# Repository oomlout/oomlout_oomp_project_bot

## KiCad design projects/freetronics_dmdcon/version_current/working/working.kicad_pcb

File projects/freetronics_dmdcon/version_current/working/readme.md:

# DMDCon by freetronics  
This is a harvested standardized copy of a project from github.  
The original project can be found at:  
https://github.com/freetronics/DMDCon  
Please consult that link for additional, details, files, and license information.  
Note: It was auto harvested and if the original repo had more than one board file or anything out of the ordinary the files here are likely not representative.

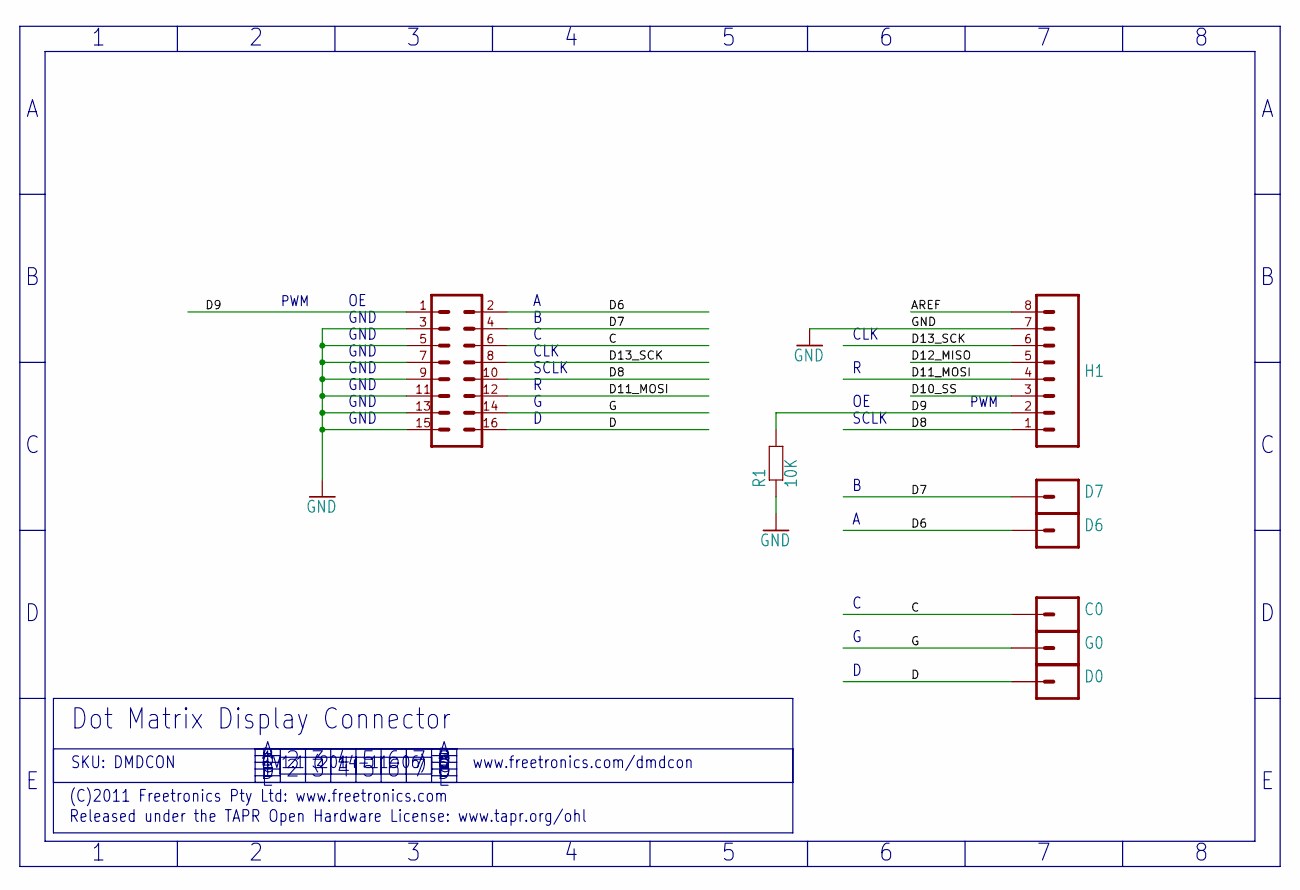
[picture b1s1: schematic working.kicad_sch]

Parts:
C0: M01PTH; 1X01
D0, D6, D7: M01PTH; 1X01
DMD0: M08X2SMALLERPADS; 2X8-SMALLERPADS
G0: M01PTH; 1X01
H1: Digital_8_13; 1X08
R1: 10K; 0805

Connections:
AREF: H1.8
C: C0.1, DMD0.6
D: D0.1, DMD0.16
D6: D6.1, DMD0.2
D7: D7.1, DMD0.4
D8: DMD0.10, H1.1
D9: DMD0.1, H1.2, R1.2
D10_SS: H1.3
D11_MOSI: DMD0.12, H1.4
D12_MISO: H1.5
D13_SCK: DMD0.8, H1.6
G: DMD0.14, G0.1
GND: DMD0.3, DMD0.5, DMD0.7, DMD0.9, DMD0.11, DMD0.13, DMD0.15, H1.7, R1.1

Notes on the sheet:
PWM
(C)2011 Freetronics Pty Ltd: www.freetronics.com
GND
CLK
www.freetronics.com/dmdcon
V1.1 (2014-11-06)
Released under the TAPR Open Hardware License: www.tapr.org/ohl
SCLK
SKU: DMDCON
Dot Matrix Display Connector

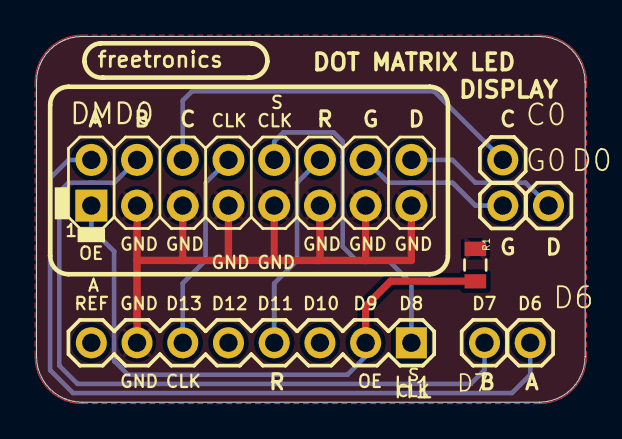
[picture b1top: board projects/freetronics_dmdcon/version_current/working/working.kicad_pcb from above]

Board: 2 copper layers, 30.5 x 20.3 mm, 8 parts (0 on the bottom side), 10 nets.

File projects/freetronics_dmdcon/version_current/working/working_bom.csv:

"Id";"Designator";"Footprint";"Quantity";"Designation";"Supplier and ref";
1;"DMD0";"2X8-SMALLERPADS";1;"M08X2";;;
2;"D7,G0,D0,C0,D6";"1X01";5;"M01PTH";;;
3;"R1";"0805";1;"10K";;;
4;"H1";"1X08";1;"Digital_8_13";;;

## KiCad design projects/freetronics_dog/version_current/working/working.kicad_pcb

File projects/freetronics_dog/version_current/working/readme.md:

# DOG by freetronics  
This is a harvested standardized copy of a project from github.  
The original project can be found at:  
https://github.com/freetronics/DOG  
Please consult that link for additional, details, files, and license information.  
Note: It was auto harvested and if the original repo had more than one board file or anything out of the ordinary the files here are likely not representative.

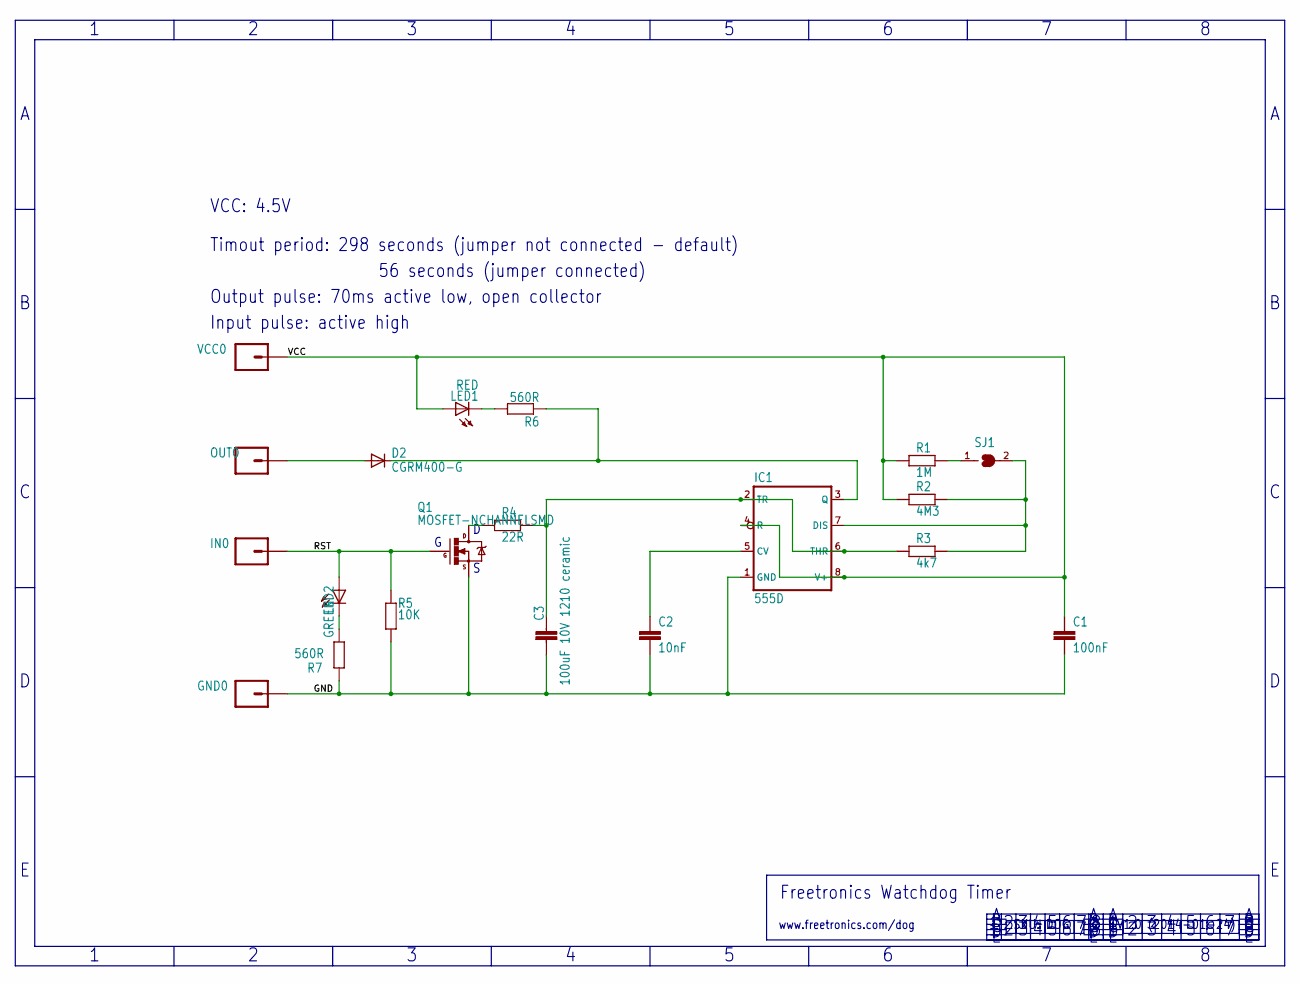
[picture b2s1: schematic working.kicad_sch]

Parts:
C1: 100nF; 0603
C2: 10nF; 0603
C3: 100uF 10V 1210 ceramic; C1210
D2: CGRM400-G; SOD-123_MINI-SMA
GND0: M01PTH; 1X01
IC1: 555D; SO08
IN0: M01PTH; 1X01
LED1: RED; LED-0603
LED2: GREEN; LED-0603
OUT0: M01PTH; 1X01
Q1: MOSFET-NCHANNELSMD; SOT23-3
R1: 1M; 0603
R2: 4M3; 0603
R3: 4k7; 0603
R4: 22R; 0603
R5: 10K; 0603
R6, R7: 560R; 0603
SJ1: SJ
VCC0: M01PTH; 1X01

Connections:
C4: C3.1, IC1.2 (TR), IC1.6 (THR), R3.1, R4.2
GND: C1.2, C2.2, C3.2, GND0.1, IC1.1 (GND), Q1.2 (S), R5.1, R7.2
unnamed: Q1.3 (D), R4.1
unnamed: LED2.C, R7.1
unnamed: R1.2, SJ1.1
unnamed: IC1.7 (DIS), R2.2, R3.2, SJ1.2
unnamed: LED1.C, R6.2
unnamed: C2.1, IC1.5 (CV)
unnamed: D2.A, OUT0.1
RST: IN0.1, LED2.A, Q1.1 (G), R5.2
TO: D2.C, IC1.3 (Q), R6.1
VCC: C1.1, IC1.4 (R), IC1.8 (V+), LED1.A, R1.1, R2.1, VCC0.1

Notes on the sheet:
V1.0 (2014-01-24)
VCC: 4.5V
www.freetronics.com/dog
Input pulse: active high
Timout period: 298 seconds (jumper not connected - default)
SKU: DOG
56 seconds (jumper connected)
Freetronics Watchdog Timer
Output pulse: 70ms active low, open collector

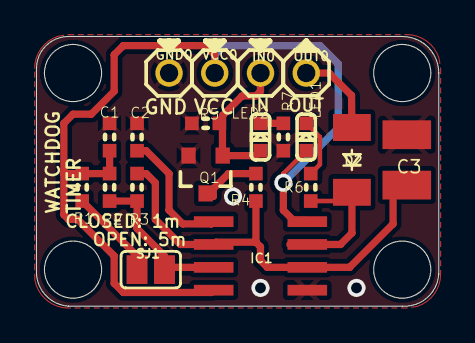
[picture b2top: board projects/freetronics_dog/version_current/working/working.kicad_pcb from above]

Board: 2 copper layers, 22.4 x 15.0 mm, 24 parts (0 on the bottom side), 12 nets.

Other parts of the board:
@HOLE0, @HOLE1, @HOLE2, @HOLE3: (no value)

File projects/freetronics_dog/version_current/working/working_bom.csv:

"Id";"Designator";"Footprint";"Quantity";"Designation";"Supplier and ref";
1;"R2";"0603";1;"4M3";;;
2;"R3";"0603";1;"4k7";;;
3;"VCC0,IN0,GND0,OUT0";"1X01";4;"M01PTH";;;
4;"@HOLE1,@HOLE0,@HOLE2,@HOLE3";"";4;"";;;
5;"C2";"0603";1;"10nF";;;
6;"IC1";"SO08";1;"LM555D";;;
7;"Q1";"SOT23-3";1;"2N7002";;;
8;"LED1";"LED-0603";1;"RED";;;
9;"R6,R7";"0603";2;"560R";;;
10;"R5";"0603";1;"10K";;;
11;"R1";"0603";1;"1M";;;
12;"SJ1";"SJ";1;"";;;
13;"C3";"C1210";1;"100uF 10V 1210 ceramic";;;
14;"LED2";"LED-0603";1;"GREEN";;;
15;"D2";"SOD-123_MINI-SMA";1;"CGRM4001-G";;;
16;"C1";"0603";1;"100nF";;;
17;"R4";"0603";1;"22R";;;

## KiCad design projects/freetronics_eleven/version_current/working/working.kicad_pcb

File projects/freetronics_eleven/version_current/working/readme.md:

# Eleven by freetronics  
This is a harvested standardized copy of a project from github.  
The original project can be found at:  
https://github.com/freetronics/Eleven  
Please consult that link for additional, details, files, and license information.  
Note: It was auto harvested and if the original repo had more than one board file or anything out of the ordinary the files here are likely not representative.

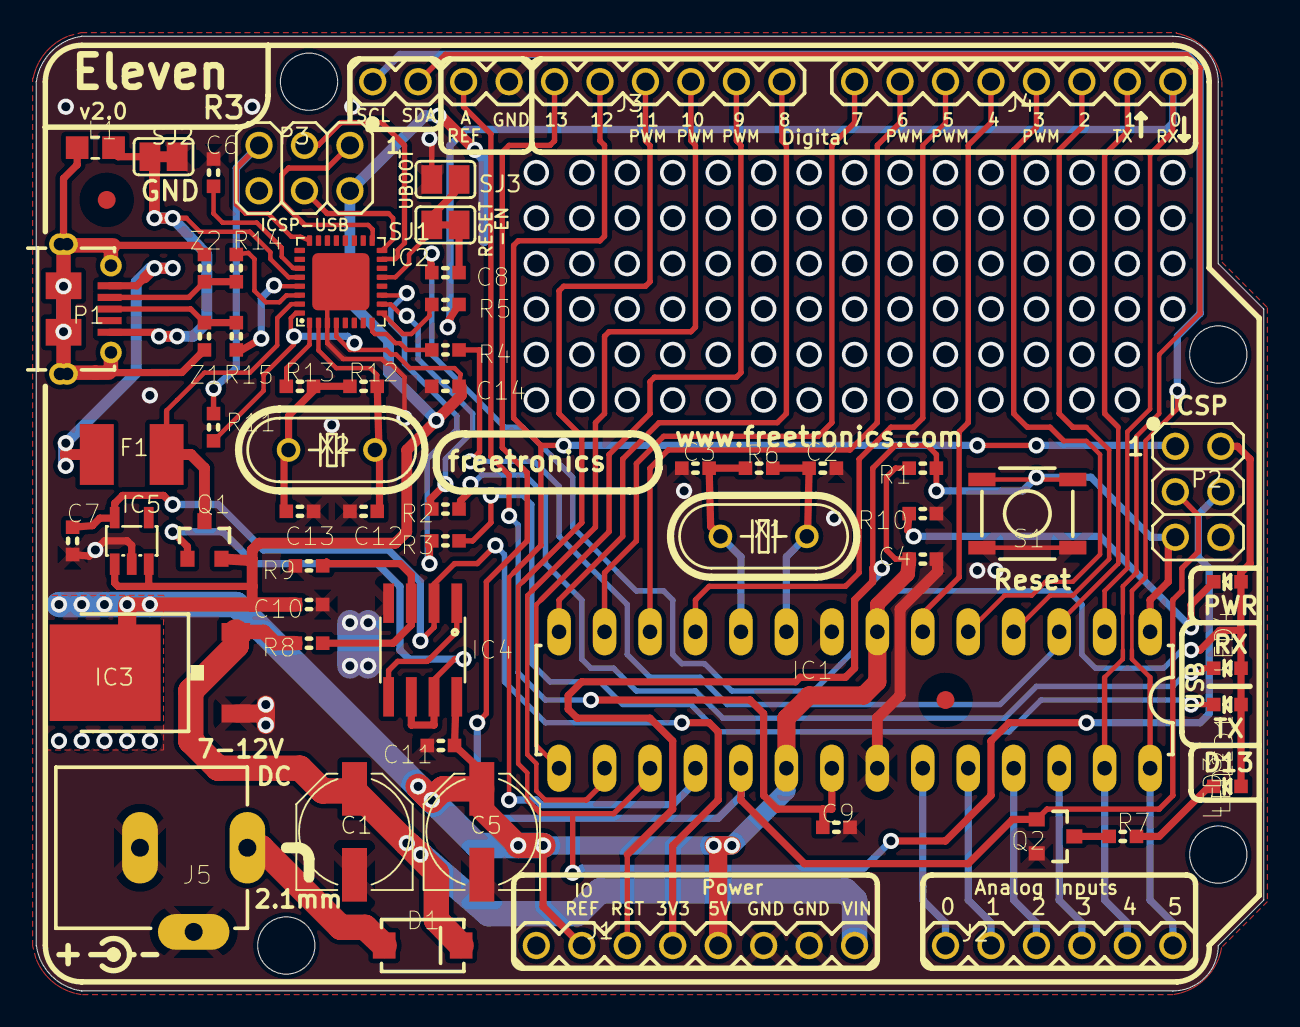
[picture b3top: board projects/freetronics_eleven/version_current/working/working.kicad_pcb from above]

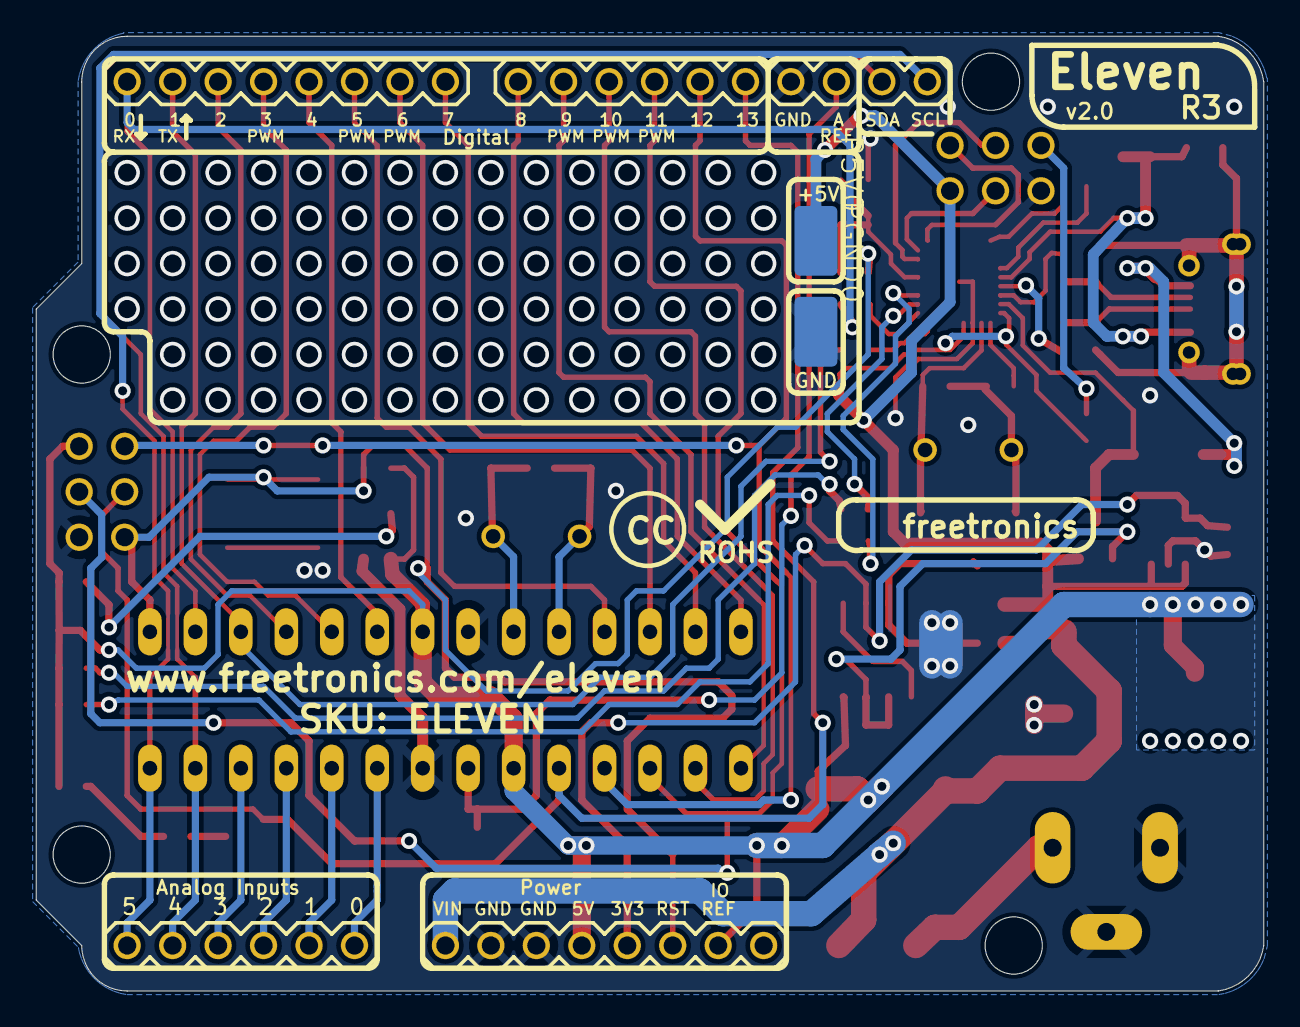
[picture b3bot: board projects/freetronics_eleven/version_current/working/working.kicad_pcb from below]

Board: 16 copper layers, 68.6 x 53.3 mm, 67 parts (2 on the bottom side), 59 nets.

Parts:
@HOLE0, @HOLE1, @HOLE2, @HOLE3: (no value)
C1, C5: 47uF 25V; PANASONIC_D
C2, C3, C12, C13: 22pF 0603; C0603
C4, C8, C9, C10, C11, C14: 100nF 0603; C0603
C6, C7: 1uF 0603; C0603
D1: 1N4004 SMB; SMA-DIODE
F1: 500mA PTC 1812; L1812
IC1: ATMEGA328P; DIL28-3
IC2: ATMEGA16U2-MU; ATMEL_QFN32
IC3: MC33269DT-5.0; DPACK
IC4: LM358D; SO08
IC5: LP2985-33DBVR; TEXAS_SOT23-DBV
J1: Power; 1X08-S
J2: Analog; 1X06-S
J3: Digital_8_13; 1X10-S
J4: Digital_0_7; 1X08-S
J5: DC_2_1MM; POWER_JACK_SLOTS
L1: 0805 INDUCTOR; 0805-LARGE
LED1: RX/GRN; LED-0603
LED2: TX/YEL; LED-0603
LED3: D13/RED; LED-0603
LED4: PWR/BLUE; LED-0603
P1: USB-6P-SMT; USB-MICROB-MB05PMXX
P2: ICSP:MAIN; 2X03PTH
P3: ICSP:USB; 2X03PTH
P5V0: LUXEON-PAD
PGND0: LUXEON-PAD
Q1: FDN340P; SOT23-3
Q2: 2N7002; SOT23-3
R1, R8, R9, R11: 10K 0603; R0603
R2, R3, R4, R5, R7, R10: 1K 0603; R0603
R6, R12: 1M 0603; R0603
R13: 27R 0603; R0603
R14, R15: 22R 0603; R0603
S1: RESET; TACTILE_SMD-6MM
SJ1: RESET-EN; SJ
SJ2: GROUND; SJ
SJ3: UBOOT; SJ
U$5, U$14: FIDUCIAL1X2.5; FIDUCIAL-1X2.5
X1, X2: 16MHz; HC49U-V
Z1, Z2: PGB1010603; TVS0603

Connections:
3V3: C7.2, IC4.2, IC5.5, J1.4
5V: C4.1, C5.+, C10.1, C11.1, C14.1, IC1.7, IC1.20, IC2.4, IC2.32, IC3.2, IC4.8, IC5.1, IC5.3, J1.2, J1.5, LED1.A, LED2.A, LED3.A, LED4.A, P2.2, P3.2, P5V0.P$1, Q1.2, R1.2, R11.2
A0: IC1.23, J2.1
A1: IC1.24, J2.2
A2: IC1.25, J2.3
A3: IC1.26, J2.4
A4_SDA: IC1.27, J2.5, J3.9
A5_SCL: IC1.28, J2.6, J3.10
AREF: C9.1, IC1.21, J3.8
D0_RX: IC1.2, J4.1, R5.1
D1_TX: IC1.3, J4.2, R4.1
D2: IC1.4, J4.3
D3: IC1.5, J4.4
D4: IC1.6, J4.5
D5: IC1.11, J4.6
D6: IC1.12, J4.7
D7: IC1.13, J4.8
D8: IC1.14, J3.1
D9: IC1.15, J3.2
D10: IC1.16, J3.3
D11_MOSI: IC1.17, J3.4, P2.4
D12_MISO: IC1.18, J3.5, P2.1
D13_SCK: IC1.19, J3.6, P2.3, Q2.1
DTR: IC2.13, SJ1.1, SJ3.2
GND: C1.-, C2.1, C3.1, C4.2, C5.-, C6.2, C7.1, C9.2, C10.2, C11.2, C12.1, C13.1, C14.2, IC1.8, IC1.22, IC2.3, IC2.EXP, IC3.1, IC4.4, IC5.2, J1.6, J1.7, J3.7, J5.GND, J5.GNDBREAK, P2.6, P3.6, PGND0.P$1, Q2.2, R9.1, R10.1, S1.1, S1.2, SJ2.2, SJ3.1
MISO2: IC2.17, P3.1
MOSI2: IC2.16, P3.4
unnamed: C8.1, SJ1.2
unnamed: IC2.1, R13.1
unnamed: L1.1, P1.FIX1, P1.FIX2, P1.PIN1, P1.PIN2, P1.TAB1, P1.TAB2, Z1.2, Z2.2
unnamed: LED3.C, R7.2
unnamed: C2.2, IC1.9, R6.2, X1.2
unnamed: Q2.3, R7.1
unnamed: C3.2, IC1.10, R6.1, X1.1
unnamed: D1.A, J5.PWR
unnamed: IC4.3, R8.1, R9.2
unnamed: IC4.1, IC4.5
unnamed: LED1.C, R2.2
unnamed: IC4.6, IC4.7, Q1.1
unnamed: LED2.C, R3.2
unnamed: LED4.C, R10.2
unnamed: P1.D+, R15.2, Z1.1
unnamed: P1.D-, R14.2, Z2.1
unnamed: C12.2, IC2.2, R12.2, X2.2
unnamed: C13.2, R12.1, R13.2, X2.1
unnamed: F1.1, P1.VBUS
unnamed: C6.1, IC2.27
RD+: IC2.29, R15.1
RD-: IC2.30, R14.1
RESET: C8.2, IC1.1, J1.3, P2.5, R1.1, S1.3, S1.4
RESET2: IC2.24, P3.5, R11.1
RXLED: IC2.10, R2.1
SCK2: IC2.15, P3.3
TXLED: IC2.11, R3.1
UGND: IC2.28, L1.2, P1.GND, SJ2.1
USBRXD: IC2.9, R5.2
USBTXD: IC2.8, R4.2
USBVCC: F1.2, IC2.31, Q1.3
VIN: C1.+, D1.C, IC3.3, J1.8, R8.2

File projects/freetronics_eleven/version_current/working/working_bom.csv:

"Id";"Designator";"Footprint";"Quantity";"Designation";"Supplier and ref";
1;"R2,R10,R4,R3,R7,R5";"R0603";6;"1K 0603";;;
2;"C8,C4,C9,C14,C10,C11";"C0603";6;"100nF 0603";;;
3;"X2,X1";"HC49U-V";2;"16MHz";;;
4;"R6,R12";"R0603";2;"1M 0603";;;
5;"R9,R8,R1,R11";"R0603";4;"10K 0603";;;
6;"J3";"1X10-S";1;"Digital_8_13";;;
7;"Q2";"SOT23-3";1;"2N7002";;;
8;"IC2";"ATMEL_QFN32";1;"ATMEGA16U2-MU";;;
9;"R13";"R0603";1;"27R 0603";;;
10;"SJ2";"SJ";1;"GROUND";;;
11;"P3";"2X03PTH";1;"ICSP:USB";;;
12;"C1,C5";"PANASONIC_D";2;"47uF 25V";;;
13;"LED1";"LED-0603";1;"RX/GRN";;;
14;"J4";"1X08-S";1;"Digital_0_7";;;
15;"L1";"0805-LARGE";1;"0805 INDUCTOR";;;
16;"LED4";"LED-0603";1;"PWR/BLUE";;;
17;"Z1,Z2";"TVS0603";2;"PGB1010603";;;
18;"C6,C7";"C0603";2;"1uF 0603";;;
19;"P1";"USB-MICROB-MB05PMXX";1;"USB-6P-SMT";;;
20;"@HOLE0,@HOLE1,@HOLE3,@HOLE2";"";4;"";;;
21;"SJ1";"SJ";1;"RESET-EN";;;
22;"F1";"L1812";1;"500mA PTC 1812";;;
23;"C3,C12,C13,C2";"C0603";4;"22pF 0603";;;
24;"J1";"1X08-S";1;"Power";;;
25;"LED2";"LED-0603";1;"TX/YEL";;;
26;"LED3";"LED-0603";1;"D13/RED";;;
27;"IC3";"DPACK";1;"MC33269DT-5.0";;;
28;"Q1";"SOT23-3";1;"FDN340P";;;
29;"J2";"1X06-S";1;"Analog";;;
30;"P2";"2X03PTH";1;"ICSP:MAIN";;;
31;"R14,R15";"R0603";2;"22R 0603";;;
32;"S1";"TACTILE_SMD-6MM";1;"RESET";;;
33;"IC5";"TEXAS_SOT23-DBV";1;"LP2985-33DBVR";;;
34;"D1";"SMA-DIODE";1;"1N4004 SMB";;;
35;"IC4";"SO08";1;"LM358D";;;
36;"U$14,U$5";"FIDUCIAL-1X2.5";2;"FIDUCIAL1X2.5";;;
37;"J5";"POWER_JACK_SLOTS";1;"DC_2_1MM";;;
38;"SJ3";"SJ";1;"UBOOT";;;
39;"IC1";"DIL28-3";1;"ATMEGA328P";;;
40;"PGND0,P5V0";"LUXEON-PAD";2;"";;;

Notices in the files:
projects/freetronics_dmdcon/version_current/working/working.kicad_pcb:
(C)2014 Freetronics Pty Ltd
projects/freetronics_eleven/version_current/working/working.kicad_sch:
(C)2012 Freetronics Pty Ltd: www.freetronics.com
projects/freetronics_esp12sh/version_current/working/working.kicad_pcb:
(c) 2015 Freetronics Pty Ltd
Open Hardware License
projects/freetronics_esp12sh/version_current/working/working.kicad_sch:
Copyright 2016 Freetronics Pty Ltd
Released under the terms of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
projects/freetronics_esp1sh/version_current/working/working.kicad_sch:
Copyright 2014-2015 Freetronics Pty Ltd
